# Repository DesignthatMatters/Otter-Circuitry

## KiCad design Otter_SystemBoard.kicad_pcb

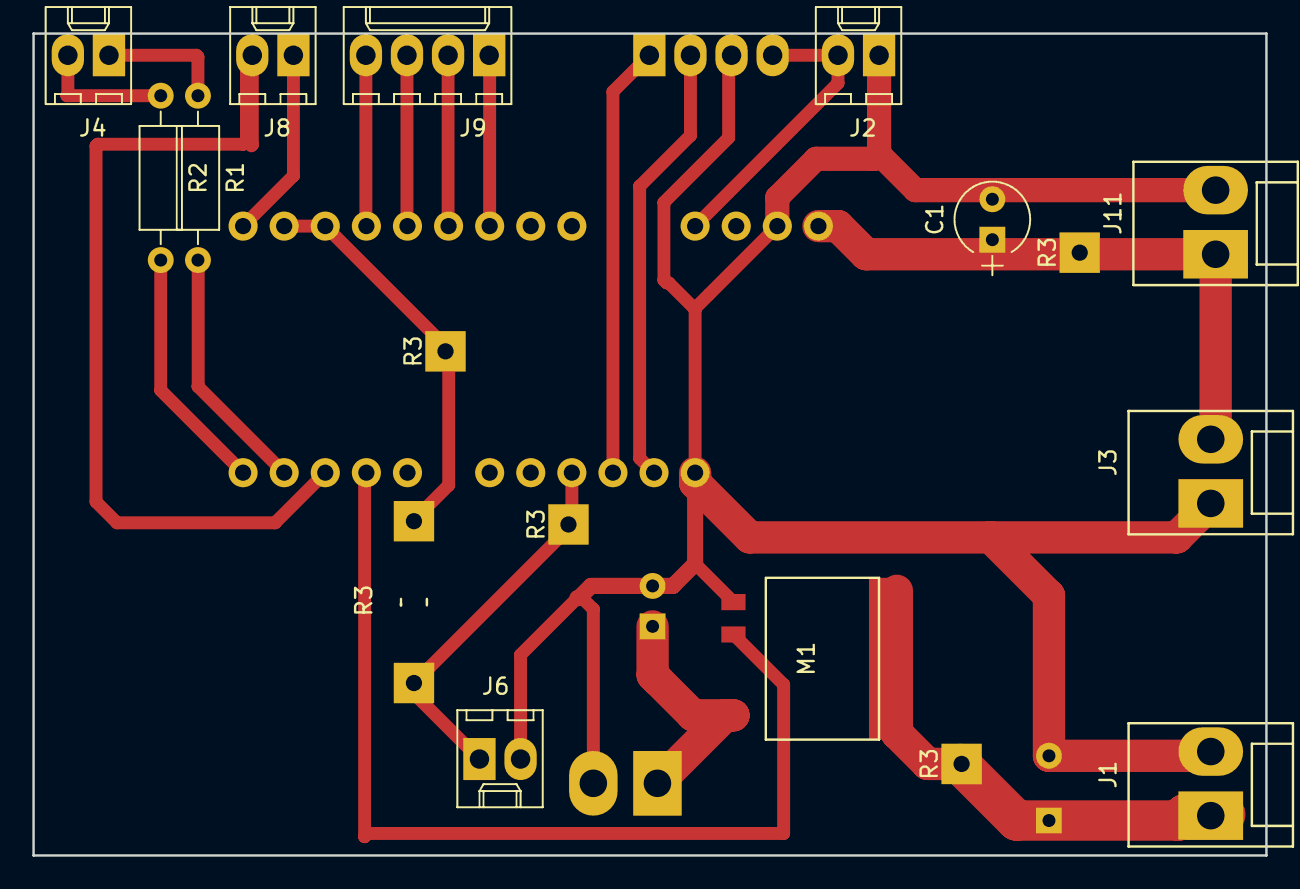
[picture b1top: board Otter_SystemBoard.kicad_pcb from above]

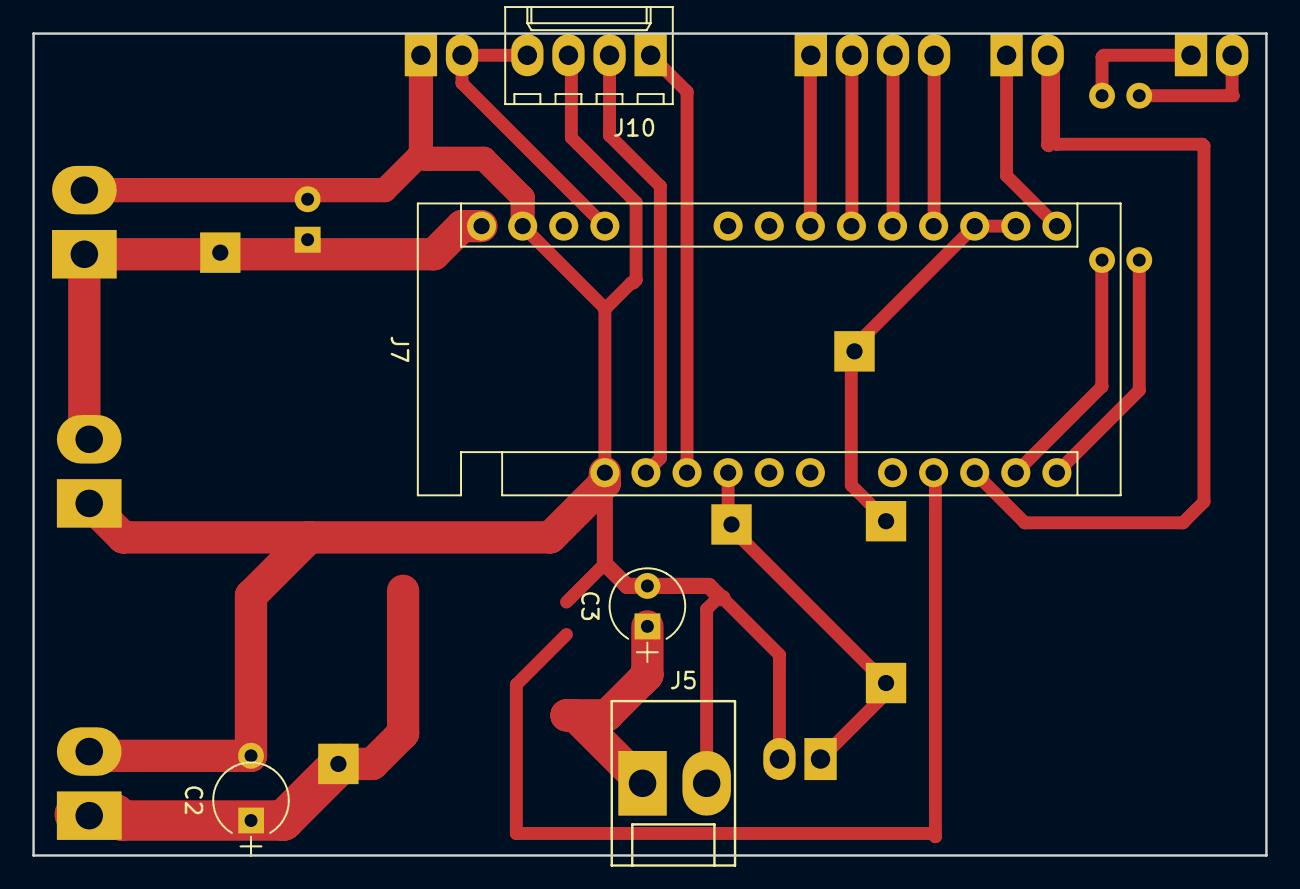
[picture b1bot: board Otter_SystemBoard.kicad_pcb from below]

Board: 2 copper layers, 76.2 x 50.8 mm, 22 parts (5 on the bottom side), 19 nets.

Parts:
C1, C2, C3: CP1; CP_Radial_Tantal_D4.5mm_P2.50mm
J1: Boost-Converter Output; Molex_KK-41791-02_02x3.96mm_Straight
J2: GND 5V Connector; Molex_KK-6410-02_02x2.54mm_Straight
J3: Boost-Converter Input; Molex_KK-41791-02_02x3.96mm_Straight
J4: LEDS; Molex_KK-6410-02_02x2.54mm_Straight
J5: OtterPower; Molex_KK-41791-02_02x3.96mm_Straight
J6: Thermistor Connector; Molex_KK-6410-02_02x2.54mm_Straight
J7: Arduino Micro; Arduino_Nano
J8: Buzzer Connector; Molex_KK-6410-02_02x2.54mm_Straight
J9: Dome Switches; Molex_KK-6410-04_04x2.54mm_Straight
J10: 7-Seg; Molex_KK-6410-04_04x2.54mm_Straight
J11: 12V Input; Molex_KK-41791-02_02x3.96mm_Straight
M1: VN750PT
R1, R2: 330; R_Axial_DIN0207_L6.3mm_D2.5mm_P10.16mm_Horizontal
R3, R3#2, R3#3: Resistor_SMD+THTuniversal_0805to1206_RM10_HandSoldering
R3#4, R3#5: 50k; Resistor_SMD+THTuniversal_0805to1206_RM10_HandSoldering

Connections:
+5V: J2.2, J10.4
+12V: J3.2, J7.Vin, J11.1
+24V: C2.1, C3.+, J1.1, M1.Vout
GND: C1.2, C2.2, C3.2, J1.2, J2.1, J3.1, J5.2, J6.2, J7.GND, J10.3, J11.2
unnamed: C1.1, J5.1
unnamed: J4.1, R1.1
unnamed: J4.2, R2.1
unnamed: J6.1, J7.A4, R3.1, R3#2.1, R3#3.1, R3#4.1, R3#5.1
unnamed: J7.3.3V, J7.AREF, R3#5.2
unnamed: J7.A0, J9.4
unnamed: J7.A1, J9.3
unnamed: J7.A2, J9.2
unnamed: J7.A3, J9.1
unnamed: J7.A5, J8.1
unnamed: J7.D4, J8.2
unnamed: J7.D11, R1.2
unnamed: J7.D12, R2.2
unnamed: J7.SDA, J10.1
unnamed: J7.SCL, J10.2

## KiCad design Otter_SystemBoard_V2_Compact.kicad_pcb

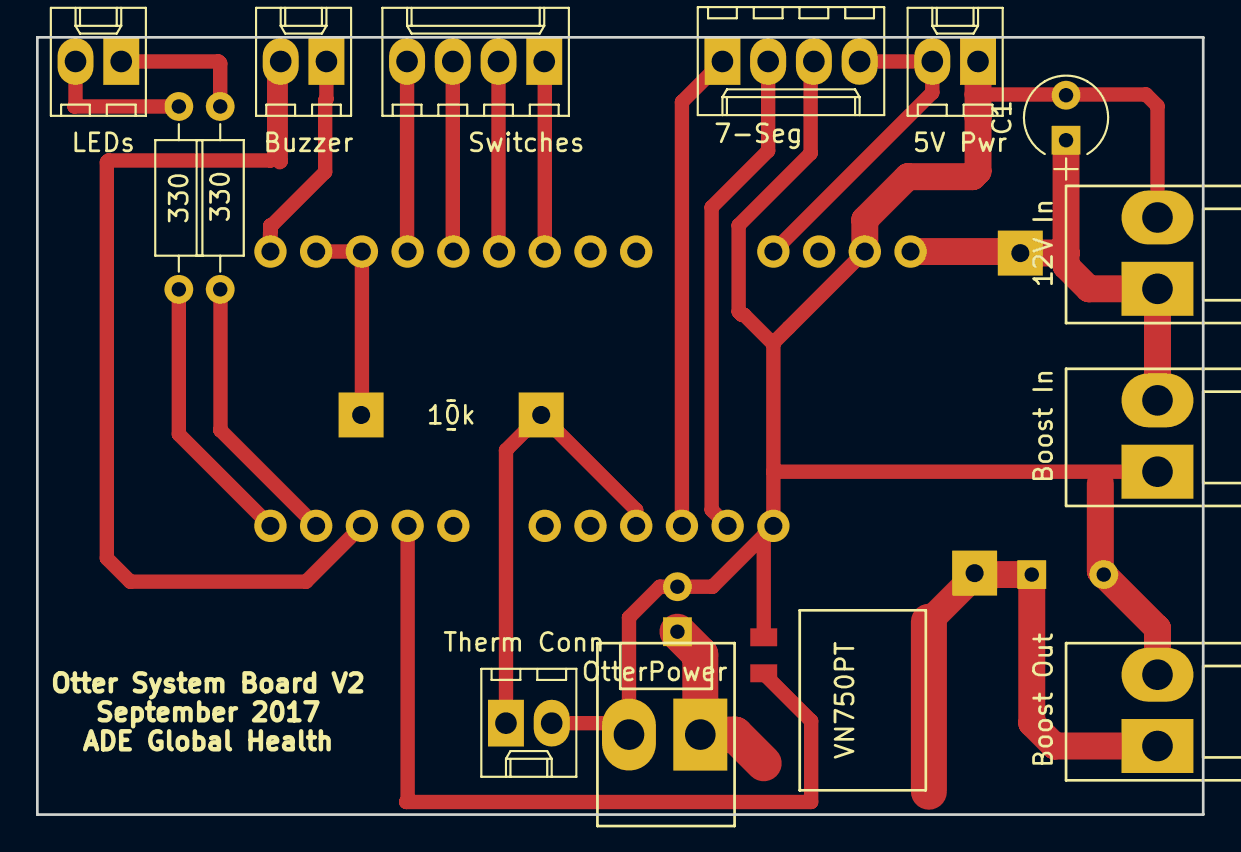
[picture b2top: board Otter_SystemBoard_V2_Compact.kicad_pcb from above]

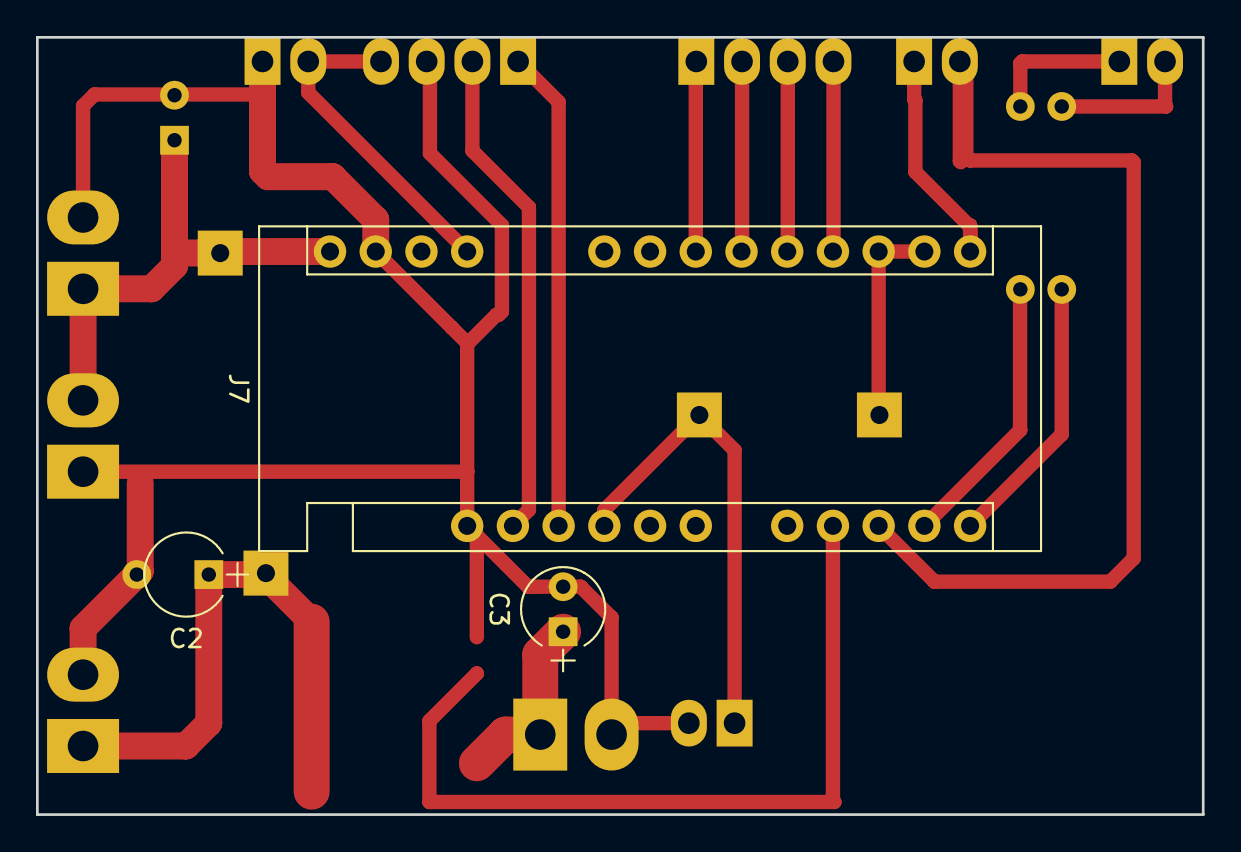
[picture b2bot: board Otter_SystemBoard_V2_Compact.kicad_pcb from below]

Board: 2 copper layers, 64.8 x 43.2 mm, 18 parts (3 on the bottom side), 18 nets.

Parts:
5V Pwr: GND 5V Connector; Molex_KK-6410-02_02x2.54mm_Straight
7-Seg: 7-Seg; Molex_KK-6410-04_04x2.54mm_Straight
10k: Resistor_SMD+THTuniversal_0805to1206_RM10_HandSoldering
12V In: 12V Input; Molex_KK-41791-02_02x3.96mm_Straight
330, 330#2: R_Axial_DIN0207_L6.3mm_D2.5mm_P10.16mm_Horizontal
Boost In: Boost-Converter Input; Molex_KK-41791-02_02x3.96mm_Straight
Boost Out: Boost-Converter Output; Molex_KK-41791-02_02x3.96mm_Straight
Buzzer: Buzzer Connector; Molex_KK-6410-02_02x2.54mm_Straight
C1, C2, C3: CP1; CP_Radial_Tantal_D4.5mm_P2.50mm
J7: Arduino Micro; Arduino_Nano
LEDs: LEDS; Molex_KK-6410-02_02x2.54mm_Straight
OtterPower: OtterPower; Molex_KK-41791-02_02x3.96mm_Straight
Switches: Dome Switches; Molex_KK-6410-04_04x2.54mm_Straight
Therm Conn: Thermistor Connector; Molex_KK-6410-02_02x2.54mm_Straight
VN750PT: VN750PT

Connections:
+5V: 5V Pwr.2, 7-Seg.4
+12V: 12V In.1, Boost In.2, C1.1, J7.Vin
+24V: Boost Out.1, C2.1, C3.+, OtterPower.1, VN750PT.Vcc, VN750PT.Vout
GND: 5V Pwr.1, 7-Seg.3, 12V In.2, Boost In.1, Boost Out.2, C1.2, C2.2, C3.2, J7.GND, OtterPower.2, Therm Conn.2, VN750PT.GND
unnamed: J7.D9, VN750PT.Inpu
unnamed: 330#2.1, LEDs.1
unnamed: 330.1, LEDs.2
unnamed: 10k.1, J7.A4, J7.D4, Therm Conn.1
unnamed: 10k.2, J7.3.3V, J7.AREF
unnamed: J7.A0, Switches.4
unnamed: J7.A1, Switches.3
unnamed: J7.A2, Switches.2
unnamed: J7.A3, Switches.1
unnamed: Buzzer.1, J7.A5
unnamed: 330#2.2, J7.D11
unnamed: 330.2, J7.D12
unnamed: 7-Seg.1, J7.SDA
unnamed: 7-Seg.2, J7.SCL

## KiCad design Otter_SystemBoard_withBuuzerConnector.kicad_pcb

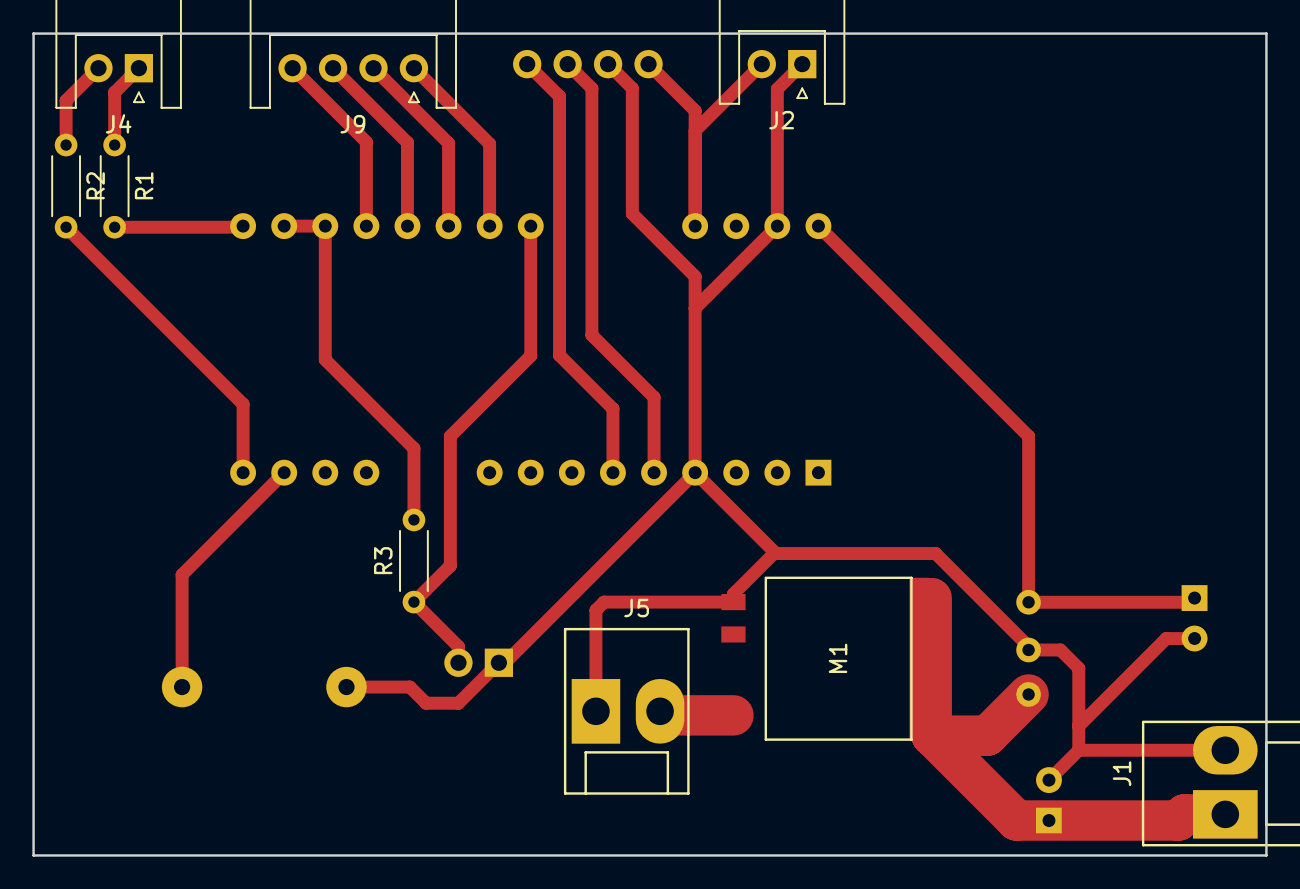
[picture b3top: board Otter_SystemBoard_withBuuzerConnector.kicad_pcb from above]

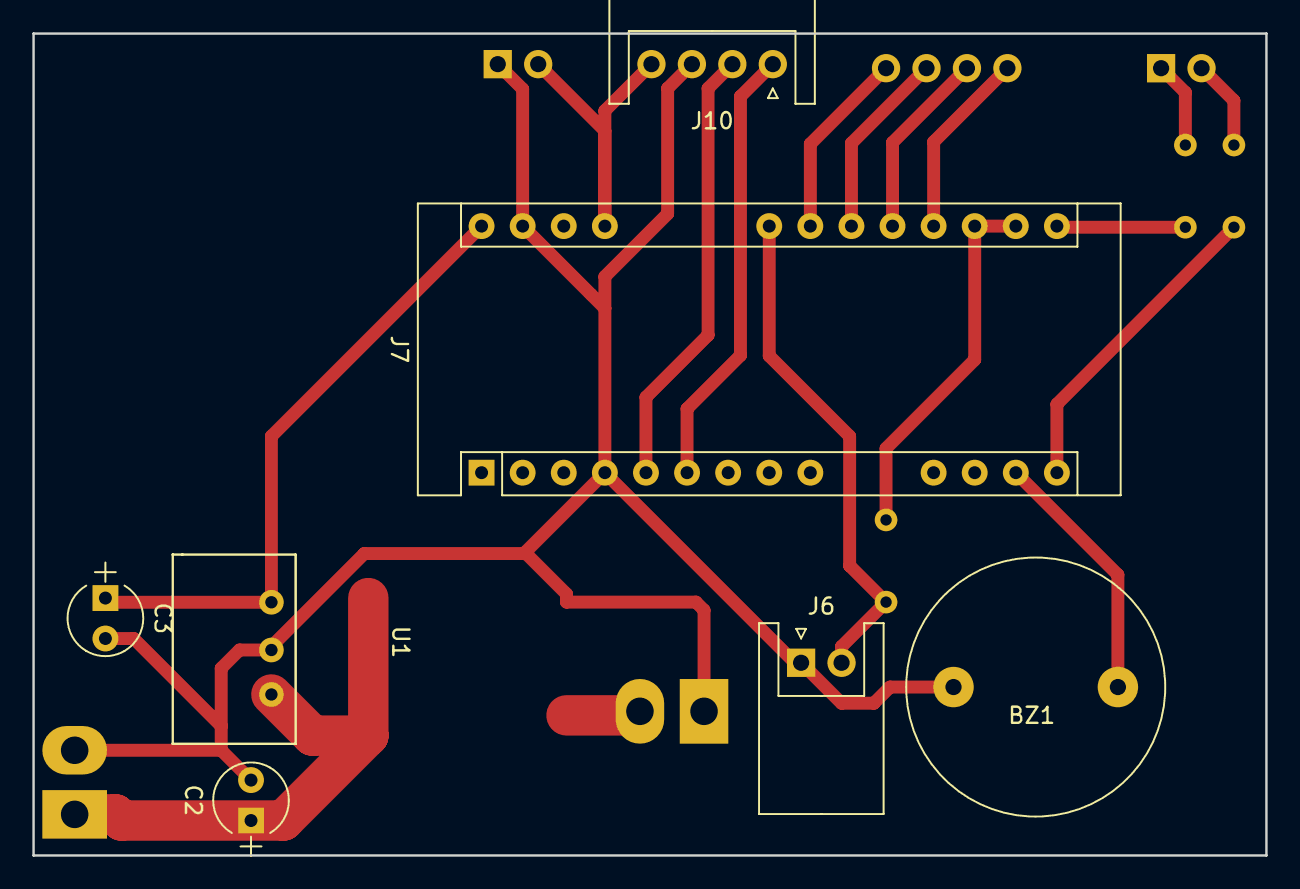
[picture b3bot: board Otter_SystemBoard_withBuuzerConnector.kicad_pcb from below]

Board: 2 copper layers, 76.2 x 50.8 mm, 16 parts (7 on the bottom side), 18 nets.

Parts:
BZ1: Buzzer; BUZZER
C2, C3: CP1; CP_Radial_Tantal_D4.5mm_P2.50mm
J1: Power; Molex_KK-41791-02_02x3.96mm_Straight
J2: GND 5V Connector; JST_XH_S02B-XH-A_02x2.50mm_Angled
J4: LEDS; JST_XH_S02B-XH-A_02x2.50mm_Angled
J5: OtterPower; Molex_KK-41791-02_02x3.96mm_Straight
J6: Thermistor Connector; JST_XH_S02B-XH-A_02x2.50mm_Angled
J7: Arduino Micro; Arduino_Nano
J9: Dome Switches; JST_XH_S04B-XH-A_04x2.50mm_Angled
J10: 7-Seg; JST_XH_S04B-XH-A_04x2.50mm_Angled
M1: VN750PT
R1, R2: 330; R_Axial_DIN0204_L3.6mm_D1.6mm_P5.08mm_Horizontal
R3: 50k; R_Axial_DIN0204_L3.6mm_D1.6mm_P5.08mm_Horizontal
U1: BuckStep-DownConverter; BuckDownConverter

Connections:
+5V: J2.2, J7.5V, J10.4
+24V: C2.1, J1.1, J5.2, M1.Vcc, M1.Vout, U1.Vin
GND: BZ1.2, C2.2, C3.2, J1.2, J2.1, J5.1, J6.1, J7.GND, J10.3, M1.GND, U1.GND
unnamed: BZ1.1, J7.D11
unnamed: C3.1, J7.Vin, U1.Vout
unnamed: J4.1, R1.1
unnamed: J4.2, R2.1
unnamed: J6.2, J7.A4, R3.1
unnamed: J7.3.3V, J7.AREF, R3.2
unnamed: J7.A0, J9.4
unnamed: J7.A1, J9.3
unnamed: J7.A2, J9.2
unnamed: J7.A3, J9.1
unnamed: J7.D10, M1.Inpu
unnamed: J7.D13, R1.2
unnamed: J7.D12, R2.2
unnamed: J7.SDA, J10.2
unnamed: J7.SCL, J10.1

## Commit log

2017-10-01 Otter System board PCB files
2017-10-01 Additional files that will hopefully complete collection
